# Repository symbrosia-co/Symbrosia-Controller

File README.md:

# The Symbrosia Controller
As originally designed, the Symbrosia Controller is a low cost, robust, controller designed for aquaculture.  Initially developed to support on-shore seaweed farming operations in Kailua Kona, Hawai'i, the Symbrosia Controller features a customized, low-cost sensor suite and integrated control functions tailored to meet the unique demands of these environments. 

In addition to commercial use, we envision the Symbrosia Controller as a powerful educational tool. By promoting literacy in electronics, programming, and agricultural management, we hope to empower individuals and communities to innovate and thrive in the agricultural sector. Our goal is to create a community where knowledge and technology are shared to drive sustainable agricultural practices and food security worldwide.

## Background
The Symbrosia controller was developed for in-house use as a lower-cost alternative to the PLC-based and commercial off-the-shelf systems we use for algae tank and bioreactor control.  In addition to controlling the tanks there were a few other needs, places where a little remote control and monitoring is invaluable.  With the availability of WiFi processors like the ESP32 automating these functions was a practical option.

Thus the Symbrosia Controller was born…  An ESP32 wedded to a circuit board that contains the most commonly needed interfaces. A water quality sensor amplifier, some temperature inputs, a couple analog inputs, along with some relays and transistor outputs for controlling external devices like valves and pumps. 

While there are commercial solutions available, we have had mixed experience with them... The available commercial controllers are expensive and tend to provide “closed garden” systems where it becomes difficult to retrieve data outside of dedicated application software.  There is also limited or no support for integrating this equipment into a wider system.  While a number of small-scale, open source solutions do exist, none of the devices we have reviewed are fully developed into robust, industrial solutions.  As a result of our experience the Symbrosia controller offers a number of key advantages…

+ Designed from the ground up as a network appliance with full WiFi access.
+ A standard industrial ModbusTCP interface, a well established interface supported by a vast array of software and solutions available in the market.
+ A simple and effective user interface allowing access to key settings.
+ A well thought out and flexible control arrangement allowing automated control of pH, temperature, or other parameters.
+ A range of inputs that address the usual aquaculture needs...
  + One fully isolated water quality amplifier (for pH, ORP, etc.)
  + Two Pt100 temperature inputs
  + Two general purpose analog inputs that can be used with 0-5V, 0-10V, or 4-20mA signals, these can also be used as simple digital inputs.
  + Two relay outputs
  + Two open collector digital outputs
+ Good calibration solutions in place for the analog inputs
+ Semi-automated pH calibration built into the software for use with 7ph, and 4pH or 10pH reference solutions.
+ A complete solution ready for deployment in real applications.  Use it as designed and published, or change the hardware or code to suit your own needs.

Communication is via 2.4GHz WiFi, thus no cabling beyond power, or perhaps your sensors is required, a very real concern when salt water is involved and locations are scattered across a large facility. 2.4GHz offers much increased range for applications that do not require the bandwidth of higher frequencies.

For remote monitoring a ModbusTCP interface is implemented.  This allows easy integration with custom software or standard industrial SCADA systems.  While most programming languages like Python have ModbusTCP libraries available to allow connections with a few lines of code.

There are many options for designing and building a device like this.  The philosophy used in the design was carefully considered...

+ The controller is designed to be constructed and maintained by anyone with modest electronics knowledge and skills. Unless changing features is desired, no programming is required to set up and use the controller.
+ Complex solutions or specialized parts were avoided.  Rather parts that are commonly available, inexpensive, and likely to remain available for some time to come were chosen for the design.
+ An open source programming platform is used so that development tools are available at no cost, specifically the Arduino platform.
+ An open source schematic capture PCB CAD package was used, specifically KiCad. The CAD files may be used or edited at no cost beyond learning to use the software.

An example of the commonly available part philosophy can be found in the display.  There was great temptation to use a newer OLED color graphical display that would be both fun and attractive.  Rather a mundane 16x2 LCD character display was chosen.  The LDC display is very standard, inexpensive, robust in outdoor settings, available from multiple vendors, and is likely to remain available for a decade or two.  Still, a version based on an OLED display may exist someday just for the fun of it.

Another good example of this is in using a development module for the ESP32 rather than laying out the ESP32 and support electronics directly onto the main PCB.  While much of the design is surface mount, larger packages were used, this allows the entire PCB to be assembled by hand with no more specialized equipment than a decent soldering iron.

Likewise using the Arduino programming platform provides an approachable simplicity that is easily learned.  A huge array of support exists on the web with a robust development community.  Libraries to support Arduino are available from many sources that allow the use of a wide array of sensors, chips, or ready to use modules.

With the controller proving its usefulness across our algae production facility a further decision was made…  To release the controller to the community as an open source device.  Symbrosia is publishing the complete plans…  Schematic, BOM, PCB, 3D models, code, and user manual.

There is nothing exotic or particularly special here.  The Symbrosia Controller is the result of taking a number of parts and solutions that are available in the community and weaving them into a well thought out and robust solution.  The controller has been a good solution for us, maybe you can use it as well.

The Symbrosia Team

## Hardware
The Symbrosia Controler is a single circuit board that measures 120 x 92mm (4.71" x 3.62").  The board mounts an LCD display, a rotaty encoder for user input, and a pair of 8 circuit headers that permit easy connection of power and field wiring.  

The PCB assembly is designed to be mounted in either a simple case for DIN rail mounting, or for direct mounting in a control panel where the display and control knob are easily accessible.  Examples of both of these mountings can be found in the documention here including 3D models for the case.

## Software
There are several software elements to the controller, all can be found in this repository.  While you may simply download everything here, an easier solution would be to install a copy of [GitHub desktop](https://desktop.github.com/download/).  Synchronizing with Github would allow you to keep an always up-to-date version available for use.

### Firmware
Firmware for the Symbrosia Controller was wriiten in the Arduino Framework for ESP-32.  The Arduino ecosystem is open source, free, and is amazing well supported by an enormous user community.  If you do not know how to use an Arduino device it is a good skill to learn, an incredibly useful tool to have in your skillset.

Compiling and downloading firmware to the controller is most easily accomplished by downloading the free [Arduino IDE](https://www.arduino.cc/en/software) and configuring it for use with the ESP32.  Additionally a few libraries will need to be loaded, this can be done with the library tool in the IDE.

### SyView
Setup and configuration is done through access to the Modbus regiaters.  Doing this by hand would be tedious.  To simplify this task SyView, a Python GUI is provided that gives easy access to all of the setup registers in an organized graphical app.  SyView also allows downloading complete configurations so they may be stored or loaded to multiple units with a single click. 

### MbMon
MbMon is a ModbusTCP data logger.  This script is often used to do simple datalogging for testing and short experiments.  An XML configuration file is used to designate a few Modbus devices on a local network.  The specified registers are monitored and if needed logged to a CSV file that can be used for data analysis.

MbMon will work with any ModbusTCP device including SymbCtrl, it can also serve as example code for writing your own logging application.

## Examples
Currently three sample systems are documented here, use these setups as is, or modify them to your own needs...

* [Tank or PBR controller](/samples/TankController/)
* [CO<sub>2</sub> Tapping Point Monitor](/samples/CO2Monitor/)
* [Weather Station](/samples/weather/)
  
Each of these designs are provided with schematics, 3D models, and setup files for the Symbrosia Controller.

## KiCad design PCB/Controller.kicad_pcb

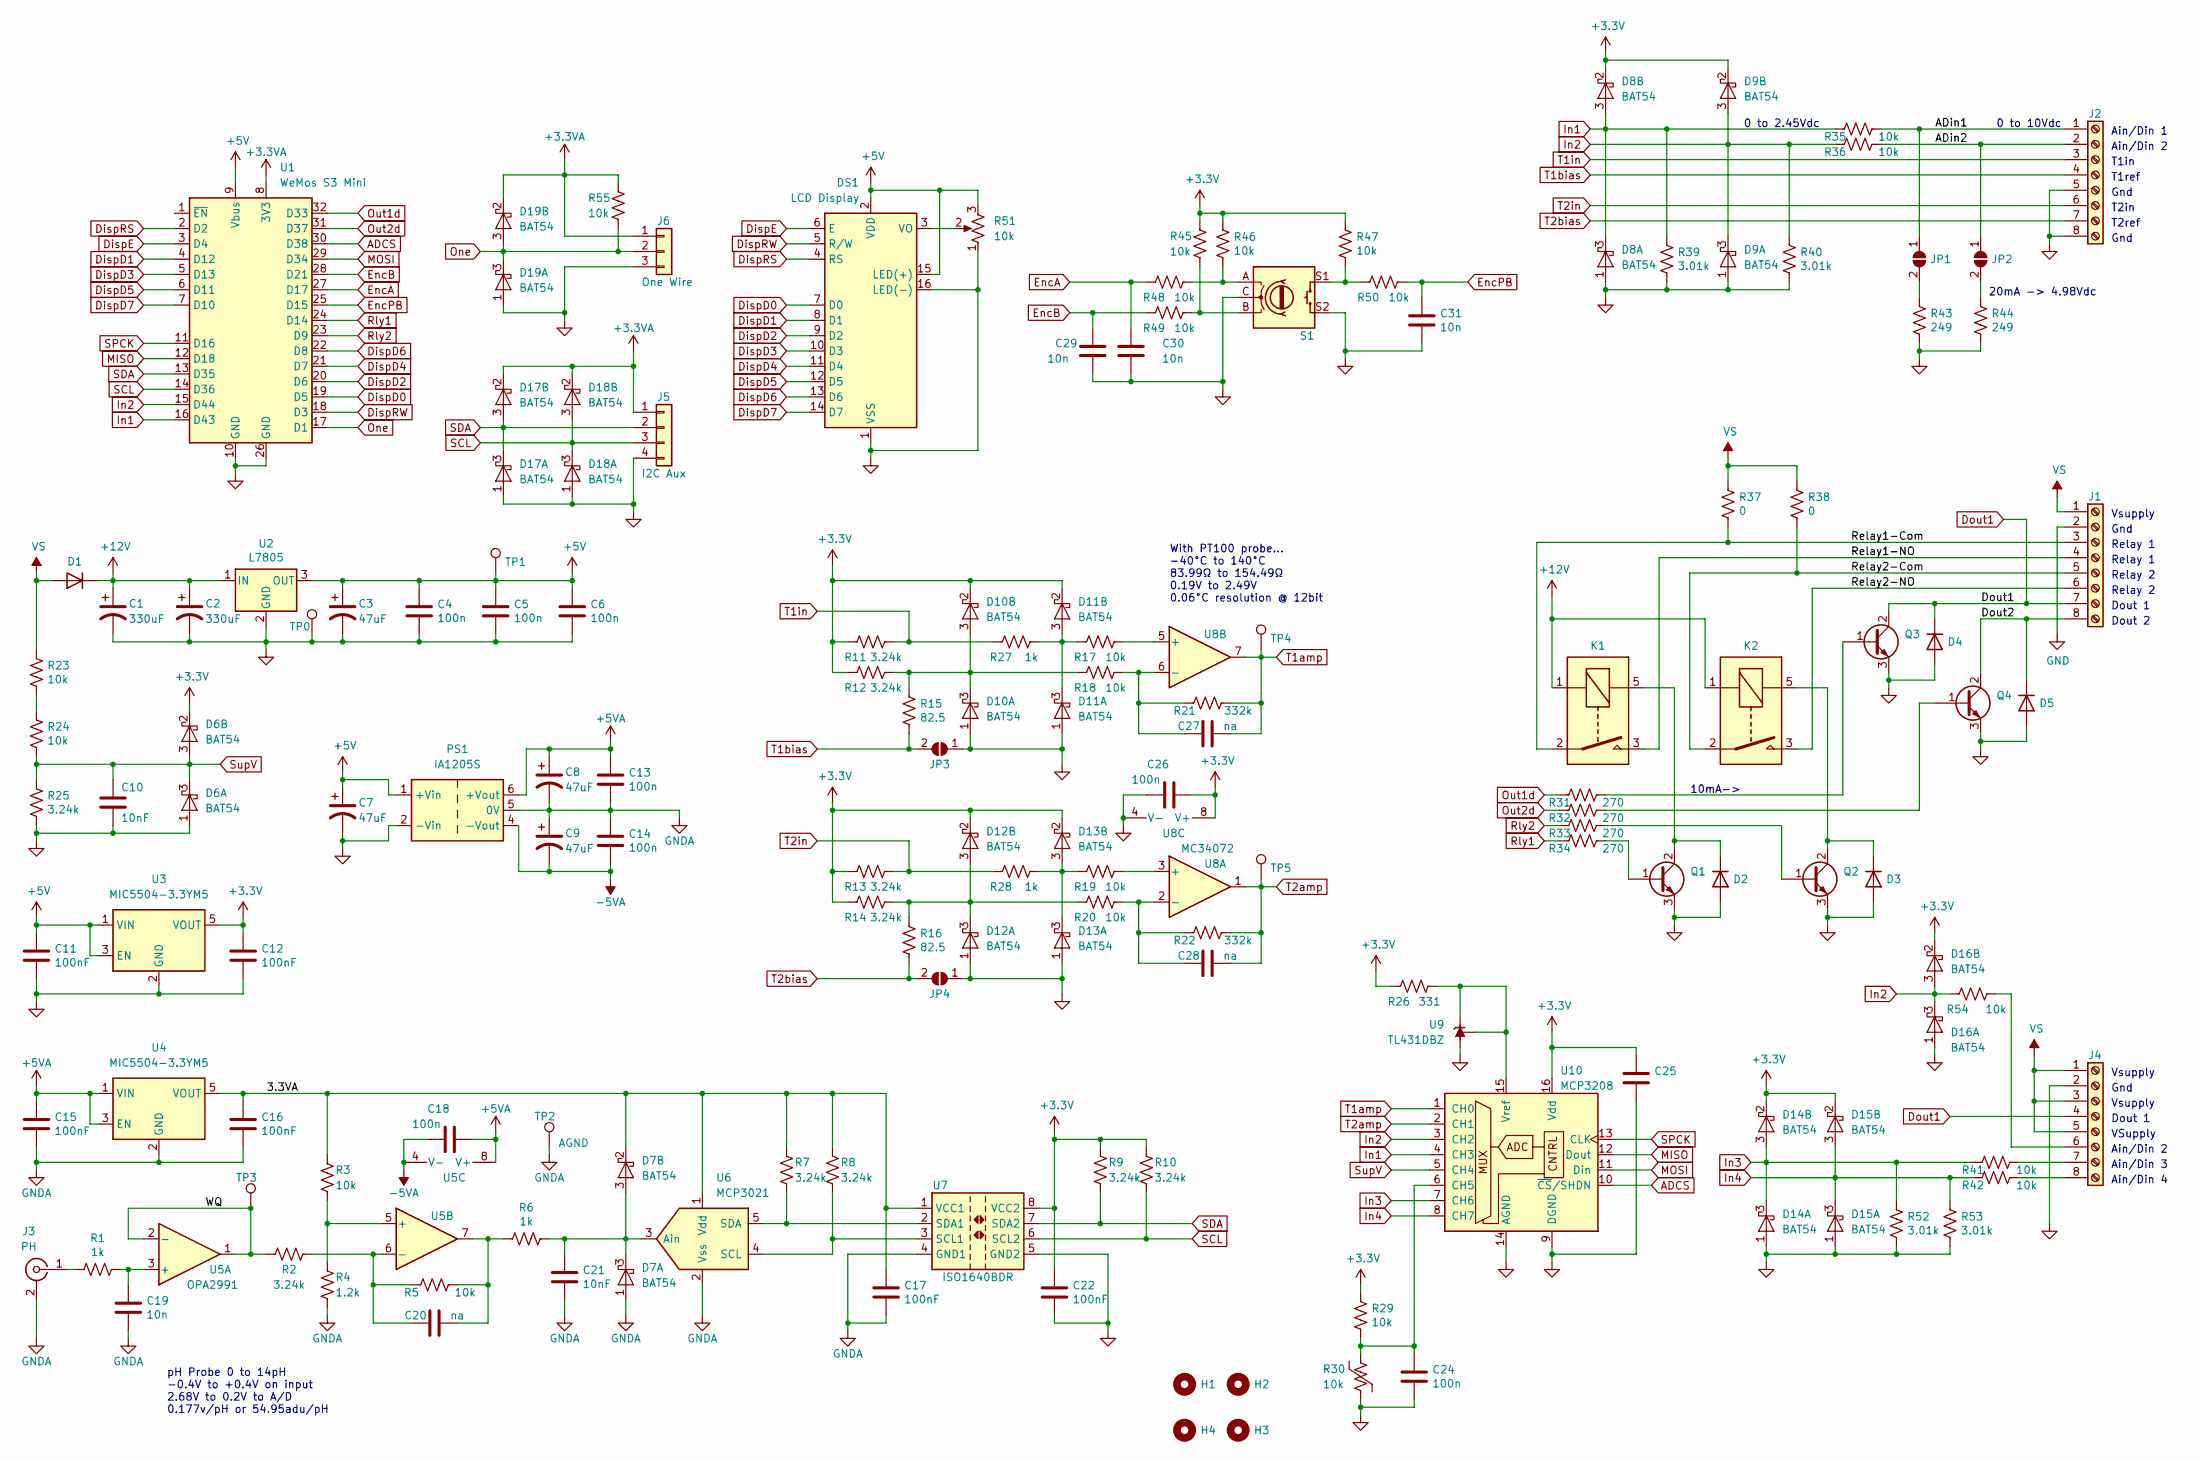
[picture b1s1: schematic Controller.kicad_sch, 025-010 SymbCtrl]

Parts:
C1, C2: 330uF; CP_Radial_D10.0mm_P5.00mm
C3, C7, C8, C9: 47uF; CP_Radial_D6.3mm_P2.50mm
C4, C5, C6, C13, C14, C18, C24, C25, C26: 100n; C_1206_3216Metric_Pad1.33x1.80mm_HandSolder
C10, C21: 10nF; C_1206_3216Metric_Pad1.33x1.80mm_HandSolder
C11, C12, C15, C16, C17, C22: 100nF; C_1206_3216Metric_Pad1.33x1.80mm_HandSolder
C19, C29, C30, C31: 10n; C_1206_3216Metric_Pad1.33x1.80mm_HandSolder
C20, C27, C28: na; C_1206_3216Metric_Pad1.33x1.80mm_HandSolder
D1, D2, D3, D4, D5: US1A; D_SMA
D6, D7, D8, D9, D10, D11, D12, D13, D14, D15, D16, D17, D18, D19: BAT54; SOT-23
DS1: LCD Display; WC1602A
H1, H2, H3, H4: MountingHole; MountingHole_3.5mm
J1, J2: Screw_Terminal_01x08; PhoenixContact_MSTBA_2,5_8-G-5,08_1x08_P5.08mm_Horizontal
J3: PH; BNC_Amphenol_B6252HB_Reversible
J4: Screw_Terminal_01x08; PhoenixContact_MSTBVA_2,5_8-G-5,08_1x08_P5.08mm_Vertical
J5: I2C Aux; Molex_KK-254_AE-6410-04A_1x04_P2.54mm_Vertical
J6: One Wire; Molex_KK-254_AE-6410-03A_1x03_P2.54mm_Vertical
JP1: In1 4-20; SolderJumper-2_P1.3mm_Open_RoundedPad1.0x1.5mm
JP2: In2 4-20; SolderJumper-2_P1.3mm_Open_RoundedPad1.0x1.5mm
JP3: T1 2/3Wire; SolderJumper-2_P1.3mm_Open_RoundedPad1.0x1.5mm
JP4: T2 2/3Wire; SolderJumper-2_P1.3mm_Open_RoundedPad1.0x1.5mm
K1, K2: TE_PCH-1xxx2M; Relay_SPST_TE_PCH-1xxx2M
PS1: IA1205S; Converter_DCDC_XP_POWER-IAxxxxS_THT
Q1, Q2, Q3, Q4: BCX56; SOT-89-3_Handsoldering
R1, R6, R27, R28: 1k; R_1206_3216Metric_Pad1.30x1.75mm_HandSolder
R2, R7, R8, R9, R10, R11, R12, R13, R14, R25: 3.24k; R_1206_3216Metric_Pad1.30x1.75mm_HandSolder
R3, R5, R17, R18, R19, R20, R23, R24, R29, R35, R36, R41, R42, R45, R46, R47, R48, R49, R50, R54, R55: 10k; R_1206_3216Metric_Pad1.30x1.75mm_HandSolder
R4: 1.2k; R_1206_3216Metric_Pad1.30x1.75mm_HandSolder
R15, R16: 82.5; R_1206_3216Metric_Pad1.30x1.75mm_HandSolder
R21, R22: 332k; R_1206_3216Metric_Pad1.30x1.75mm_HandSolder
R26: 331; R_1206_3216Metric_Pad1.30x1.75mm_HandSolder
R30: 10k; R_0805_2012Metric_Pad1.20x1.40mm_HandSolder
R31, R32, R33, R34: 270; R_1206_3216Metric_Pad1.30x1.75mm_HandSolder
R37, R38: 0; R_1206_3216Metric_Pad1.30x1.75mm_HandSolder
R39, R40, R52, R53: 3.01k; R_1206_3216Metric_Pad1.30x1.75mm_HandSolder
R43, R44: 249; R_1210_3225Metric_Pad1.30x2.65mm_HandSolder
R51: 10k; Potentiometer_Piher_PT-6-V_Vertical_Hole
S1: RotaryEncoder_Switch; RotaryEncoder_Alps_EC11E-Switch_Vertical_H20mm_CircularMoun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
TP0: Gnd; TestPoint_THTPad_D2.5mm_Drill1.2mm
TP1: +5V; TestPoint_THTPad_D2.5mm_Drill1.2mm
TP2: AGND; TestPoint_THTPad_D2.5mm_Drill1.2mm
TP3: WQ; TestPoint_THTPad_D2.5mm_Drill1.2mm
TP4: Temp2; TestPoint_THTPad_D2.5mm_Drill1.2mm
TP5: Temp1; TestPoint_THTPad_D2.5mm_Drill1.2mm
U1: WeMos S3 Mini; WEMOS S2 Mini
U2: L7805; TO-220-3_Horizontal_TabDown
U3, U4: MIC5504-3.3YM5; SOT-23-5_HandSoldering
U5: OPA2991; SOIC-8_3.9x4.9mm_P1.27mm
U6: MCP3021; SOT-23-5_HandSoldering
U7: ISO1640BDR; SO-8_3.9x4.9mm_P1.27mm
U8: MC34072; SOIC-8_3.9x4.9mm_P1.27mm
U9: TL431DBZ; SOT-23
U10: MCP3208; SOIC-16_3.9x9.9mm_P1.27mm

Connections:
+3.3V: C12.1, C22.1, C25.1, C26.1, D6.2 (K), D8.2 (K), D9.2 (K), D10.2 (K), D11.2 (K), D12.2 (K), D13.2 (K), D14.2 (K), D15.2 (K), D16.2 (K), R9.1, R10.1, R11.1, R12.1, R13.1, R14.1, R26.1, R29.2, R45.2, R46.2, R47.2, U3.5 (VOUT), U7.8 (VCC2), U8.8 (V+), U10.16 (Vdd)
+3.3VA: D17.2 (K), D18.2 (K), D19.2 (K), J5.1, J6.1, R55.2, U1.8 (3V3)
+5V: C3.1, C4.1, C5.1, C6.1, C7.1, C11.1, DS1.2 (VDD), DS1.15 (LED(+)), PS1.1 (+Vin), R51.3, TP1.1, U1.9 (Vbus), U2.3 (OUT), U3.1 (VIN), U3.3 (EN)
+5VA: C8.1, C13.1, C15.1, C18.1, PS1.6 (+Vout), U4.1 (VIN), U4.3 (EN), U5.8 (V+)
+12V: C1.1, C2.1, D1.1 (K), K1.1, K2.1, U2.1 (IN)
-5VA: C9.2, C14.2, C18.2, PS1.4 (-Vout), U5.4 (V-)
/3.3VA: C16.1, C17.1, D7.2 (K), R3.1, R7.1, R8.1, U4.5 (VOUT), U6.1 (Vdd), U7.1 (VCC1)
/ADin1: J2.1, JP1.1 (A), R35.2
/ADin2: J2.2, JP2.1 (A), R36.2
/Dout2: D5.1 (K), J1.8, Q4.2 (C)
/Relay1-Com: J1.3, K1.2, R37.1
/Relay1-NO: J1.4, K1.3
/Relay2-Com: J1.5, K2.2, R38.1
/Relay2-NO: J1.6, K2.3
/WQ: R2.2, TP3.1, U5.1, U5.2 (-)
ADCS: U1.30 (D38), U10.10 (~CS/SHDN)
DispD0: DS1.7 (D0), U1.19 (D5)
DispD1: DS1.8 (D1), U1.4 (D12)
DispD2: DS1.9 (D2), U1.20 (D6)
DispD3: DS1.10 (D3), U1.5 (D13)
DispD4: DS1.11 (D4), U1.21 (D7)
DispD5: DS1.12 (D5), U1.6 (D11)
DispD6: DS1.13 (D6), U1.22 (D8)
DispD7: DS1.14 (D7), U1.7 (D10)
DispE: DS1.6 (E), U1.3 (D4)
DispRS: DS1.4 (RS), U1.2 (D2)
DispRW: DS1.5 (R/W), U1.18 (D3)
Dout1: D4.1 (K), J1.7, J4.4, Q3.2 (C)
EncA: C30.1, R48.1, U1.27 (D17)
EncB: C29.1, R49.1, U1.28 (D21)
EncPB: C31.1, R50.2, U1.25 (D15)
GND: C1.2, C2.2, C3.2, C4.2, C5.2, C6.2, C7.2, C10.2, C11.2, C12.2, C22.2, C24.2, C25.2, C26.2, C29.2, C30.2, C31.2, D2.2 (A), D3.2 (A), D4.2 (A), D5.2 (A), D6.1 (A), D8.1 (A), D9.1 (A), D10.1 (A), D11.1 (A), D12.1 (A), D13.1 (A), D14.1 (A), D15.1 (A), D16.1 (A), D17.1 (A), D18.1 (A), D19.1 (A), DS1.1 (VSS), DS1.16 (LED(-)), J1.2, J2.5, J2.8, J4.2, J5.4, J6.3, JP3.1 (A), JP4.1 (A), PS1.2 (-Vin), Q1.3 (E), Q2.3 (E), Q3.3 (E), Q4.3 (E), R25.1, R30.2, R39.1, R40.1, R43.1, R44.1, R51.1, R52.1, R53.1, S1.C, S1.S2, TP0.1, U1.10 (GND), U1.26 (GND), U2.2 (GND), U3.2 (GND), U7.5 (GND2), U8.4 (V-), U9.3 (A), U10.9 (DGND), U10.14 (AGND)
GNDA: C8.2, C9.1, C13.2, C14.1, C15.2, C16.2, C17.2, C19.2, C21.2, D7.1 (A), J3.2 (Ext), PS1.5 (0V), R4.2, TP2.1, U4.2 (GND), U6.2 (Vss), U7.4 (GND1)
In1: D8.3 (COM), R35.1, R39.2, U1.16 (D43), U10.4 (CH3)
In2: D9.3 (COM), D16.3 (COM), R36.1, R40.2, R54.1, U1.15 (D44), U10.3 (CH2)
In3: D14.3 (COM), R41.1, R52.2, U10.7 (CH6)
In4: D15.3 (COM), R42.1, R53.2, U10.8 (CH7)
MISO: U1.12 (D18), U10.12 (Dout)
MOSI: U1.29 (D34), U10.11 (Din)
unnamed: C20.1, R5.2, R6.2, U5.7
unnamed: D2.1 (K), K1.5, Q1.2 (C)
unnamed: D3.1 (K), K2.5, Q2.2 (C)
unnamed: C21.1, D7.3 (COM), R6.1, U6.3 (Ain)
unnamed: D10.3 (COM), R12.2, R15.2, R18.1
unnamed: D11.3 (COM), R17.1, R27.2
unnamed: D12.3 (COM), R14.2, R16.2, R20.1
unnamed: D13.3 (COM), R19.1, R28.2
unnamed: DS1.3 (VO), R51.2
unnamed: J3.1 (In), R1.2
unnamed: J4.6, R54.2
unnamed: J4.7, R41.2
unnamed: J4.8, R42.2
unnamed: JP1.2 (B), R43.2
unnamed: JP2.2 (B), R44.2
unnamed: Q1.1 (B), R34.2
unnamed: Q2.1 (B), R33.2
unnamed: Q3.1 (B), R31.2
unnamed: Q4.1 (B), R32.2
unnamed: R23.1, R24.2
unnamed: R45.1, R49.2, S1.B
unnamed: R46.1, R48.2, S1.A
unnamed: R47.1, R50.1, S1.S1
unnamed: C19.1, R1.1, U5.3 (+)
unnamed: R3.2, R4.1, U5.5 (+)
unnamed: C20.2, R2.1, R5.1, U5.6 (-)
unnamed: R8.2, U6.4 (SCL), U7.3 (SCL1)
unnamed: R7.2, U6.5 (SDA), U7.2 (SDA1)
unnamed: R19.2, U8.3 (+)
unnamed: C28.2, R20.2, R22.1, U8.2 (-)
unnamed: R17.2, U8.5 (+)
unnamed: C27.2, R18.2, R21.1, U8.6 (-)
unnamed: C24.1, R29.1, R30.1, U10.6 (CH5)
unnamed: R26.2, U9.1 (K), U9.2 (REF), U10.15 (Vref)
One: D19.3 (COM), J6.2, R55.1, U1.17 (D1)
Out1d: R31.1, U1.32 (D33)
Out2d: R32.1, U1.31 (D37)
Rly1: R34.1, U1.24 (D14)
Rly2: R33.1, U1.23 (D9)
SCL: D18.3 (COM), J5.3, R10.2, U1.14 (D36), U7.6 (SCL2)
SDA: D17.3 (COM), J5.2, R9.2, U1.13 (D35), U7.7 (SDA2)
SPCK: U1.11 (D16), U10.13 (CLK)
SupV: C10.1, D6.3 (COM), R24.1, R25.2, U10.5 (CH4)
T1amp: C27.1, R21.2, TP4.1, U8.7, U10.1 (CH0)
T1bias: J2.4, JP3.2 (B), R15.1
T1in: J2.3, R11.2, R27.1
T2amp: C28.1, R22.2, TP5.1, U8.1, U10.2 (CH1)
T2bias: J2.7, JP4.2 (B), R16.1
T2in: J2.6, R13.2, R28.1
VS: D1.2 (A), J1.1, J4.1, J4.3, J4.5, R23.2, R37.2, R38.2

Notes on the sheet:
Gnd
Ain/Din 4
Dout 1
0 to 2.45Vdc
Relay 2
T2in
Vsupply
T2ref
20mA -> 4.98Vdc
Ain/Din 1
T1in
Relay 1
Ain/Din 2
pH Probe 0 to 14pH -0.4V to +0.4V on input 2.68V to 0.2V to A/D 0.177v/pH or 54.95adu/pH
VSupply
Ain/Din 3
10mA->
0 to 10Vdc
Dout 2
With PT100 probe... -40°C to 140°C 83.99Ω to 154.49Ω 0.19V to 2.49V 0.06°C resolution @ 12bit
T1ref

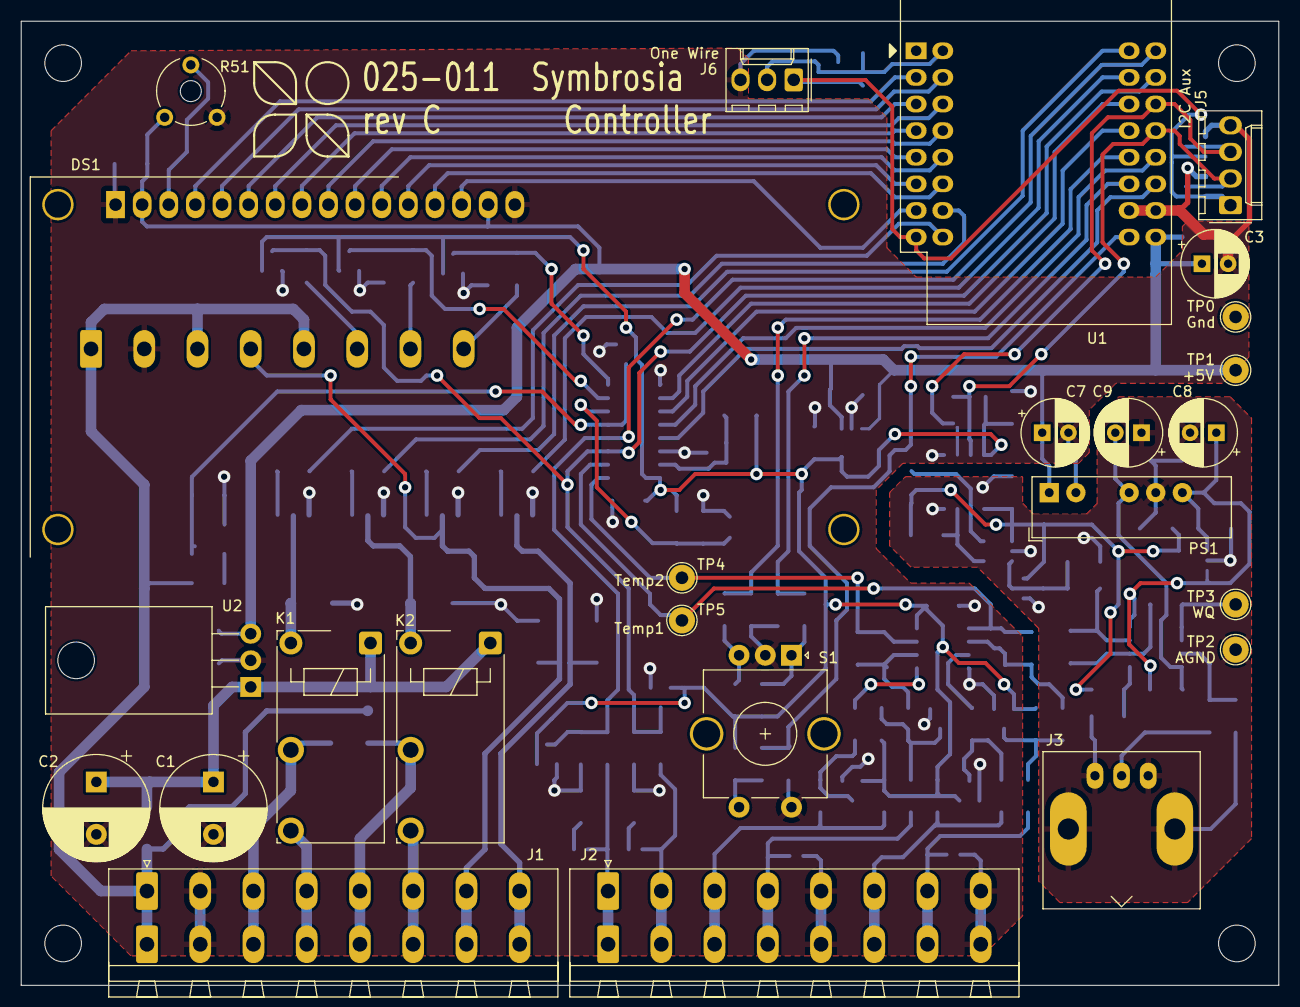
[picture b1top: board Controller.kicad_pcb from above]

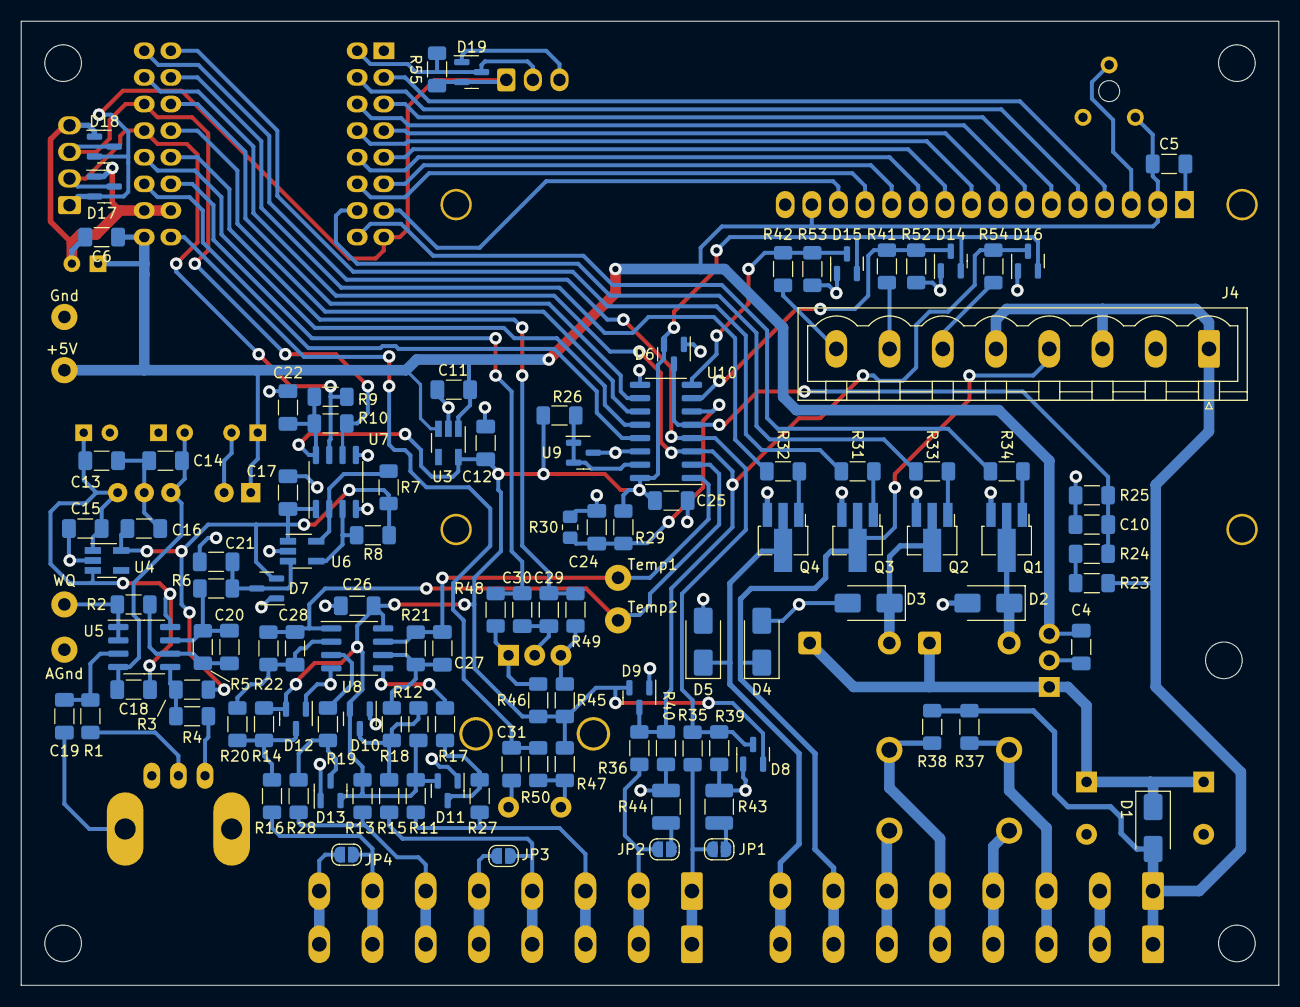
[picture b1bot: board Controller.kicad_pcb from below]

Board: 2 copper layers, 120.0 x 92.0 mm, 143 parts (114 on the bottom side), 89 nets.

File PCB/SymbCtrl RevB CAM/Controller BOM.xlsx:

Comment | Designator | Footprint | JLCPCB
Ceramic capacitor, 100nF 50V 1206 | C4, C5, C6, C10, C11, C12, C13, C14, C15, C16, C17, C18, C22, C24, C25, C26 | 1206 | C24497
Ceramic capacitor, 10nF 50V 1206 | C21, C29, C30, C31 | 1206 | C521245
Ceramic capacitor, 1nF 50V 1206 | C20, C27, C28 | 1206 | C107207
Rectifier diode, 100V 1A SMA | D1, D2, D3, D4, D5 | SMA | C156295
Schottky diode 30V 100mA dual series SOT23 | D6, D7, D8, D9, D10, D11, D12, D13 | SOT-23 | C47546
NPN Transistor 40V 1A SOT89 | Q1, Q2, Q3, Q4 | SOT-89-3 | C460011
1.00kΩ 1% resistor, 1/4W 1206 | R1, R6, R27, R28, R31, R32, R33, R34 | 1206 | C131398
3.24kΩ 1% resistor, 1/4W 1206 | R2, R7, R8, R9, R10, R11, R12, R13, R14, R25 | 1206 | C488775
10.0kΩ 1% resistor, 1/4W 1206 | R3, R5, R17, R18, R19, R20, R23, R24, R29, R35, R36, R45, R46, R47, R48, R49, R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 | 1206 | C132649
1.20kΩ 1% resistor, 1/4W 1206 | R4 | 1206 | C185265
82.5Ω 1% resistor, 1/4W 1206 | R15, R16 | 1206 | C229817
332kΩ 1% resistor, 1/4W 1206 | R21, R22 | 1206 | C137311
331Ω 1% resistor, 1/4W 1206 | R26 | 1206 | C114944
10kΩ thermistor 1206 B25/85 3630K | R30 | 1208 | C525390
3.01kΩ 1% resistor, 1/4W 1206 | R39, R40 | 1206 | C229594
249Ω 1% resistor, 1/2W 1210 | R43, R44 | 1210 | C723700
MIC5504 3.3V regulator, SOT23 | U3, U4 | SOT-23-5 | C88419
Dual op-amp, low Ib, SOIC-8 | U5, U8 | SOIC-8 | C2878324
MCP3021 10bit AtoD, SOT23-5 | U6 | SOT-23-5 | C128576
ISO1640BDR isolated I2C | U7 | SOIC-8 | C5122339
TL431 programmable voltage reference, SOIC-8 | U9 | SOIC-8 | C6970
MCP3208 12 bit 8 channel AtoD | U10 | SOIC-16 | C16939

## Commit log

2024-08-03 Update LICENSE.md
    Use GPLv3
2024-08-03 Create SymbCtrl.ino
    Added to GitHub
2024-08-03 Add files via upload
    Add source files to GitHub
2024-08-03 Add files via upload
    Add user manual to repository
2024-08-03 Update LICENSE.md
    Add full text for GPLv3
2024-08-03 Create resources
2024-08-03 Add files via upload
    Add a couple photos of the controller
2024-08-03 Add files via upload
    Smaller version of the photos
2024-08-03 Update README.md
    Further work on the readme
2024-08-03 Create README.md
    Initial outline written
2024-08-03 Update README.md
    Add more material
2024-08-04 Delete src directory
    Rearrange to make downloading to the Arduino IDE possible
2024-08-04 Create README.md
    Rearrange to make integration with Arduino IDE possible
2024-08-04 Create README.md
    New content
2024-08-04 Add files via upload
    Initial commit
2024-08-04 Delete SyView/lib/symbCtrlModbus.py.bak
    Not needed
2024-08-04 Delete SyView/lib/__pycache__ directory
    Not needed
2024-08-04 Update README.md
    Inital version
2024-08-04 Create README.md
    Initial version
2024-08-04 Update README.md
    Initial version
2024-08-04 Initial upload
2024-08-05 Add units
2024-08-05 Link latest from development PC
2024-08-05 Mods ro analogCtrl
    Added auto I2C address search to analogCtrl for MCP3021
2024-08-06 Add MBMon to repository
2024-08-08 Add some comments
2024-08-25 Add Weather
2024-08-25 Ignore configuration files
2024-09-01 Weather development
2024-09-04 Update ignore
2024-09-26 Config file update
2024-09-27 PBR Example
2024-09-27 Add STL files for PBR Controller
2024-09-27 Remove spaces from filenames
2024-09-27 Add PBR documentation
2024-10-09 Working on v2.7
2024-10-24 Create SyCheck
2024-10-24 Work on SyCheck
2024-10-24 Working on 2.7
2024-10-26 SyCheck Work
2024-10-26 Weather data
2024-10-28 v2.7 work
2024-10-28 Edit revision record
2024-10-29 Finalizing v2.7
2024-10-31 SyCheck v0.2
2024-10-31 SyView fixes
2024-11-01 Remove logfiles
2024-11-01 Version 2.7 work
2024-11-02 Regression test v2.7
2024-11-02 Edit rev record
2024-11-02 Set up FOTA
2024-11-02 Sync main
2024-11-02 Remove crud
2024-11-02 Revert "Edit rev record"
    This reverts commit 24d97c7264457223542c1ffbeaa103c3e2f5fb02.
2024-11-02 Rev check on v2.7
2024-11-02 QA on main after v2.7 merge
2024-11-05 v2.8 work
2024-11-07 Add Echo logic to memory.h limits
2024-11-14 SyView 1.3
    Add manual IP address selection
2024-11-15 Final v2.8!!
    FOTA is now operational, version needs a final regression test
2024-11-16 Fixes to v2.8 prerelease
2024-11-16 Prerelease v2.8 fixes
2024-11-18 Bug hunt in v2.8
2024-11-18 Work on v2.8
2024-11-18 Testing v2.8
2024-11-18 JSON Update
2024-11-19 v2.8 Final
2024-11-19 Update Binaries
2024-11-19 Add PCB image
2024-11-19 Cleanup uneeded filed
2024-11-21 Update comments
2025-04-15 Scrollable data frame
2025-04-16 Bind mouse wheel to scrolling
2025-04-18 Sync it
2025-04-25 Tweaks to MBMon
2025-04-30 MBMon Work v1.3
2025-05-03 MBMon work
2025-05-09 MBMon2 Work
2025-05-10 MBMon2 Work
    Nearing release of MBMon2
2025-05-11 MBMon Fix Scrolling
2025-05-11 MBMon bughunting
2025-05-15 SymbCtrl v2.9 work
2025-05-16 Update LinkedCtrl
2025-05-29 SyScan library module work
2025-05-30 SyView 2.0 work
2025-05-30 Release SyView 2.0 and Cleanup
2025-05-30 SyView 2.0 Release
2025-05-30 Backup Old MBMon
2025-06-03 Add PCB to repository
2025-06-04 PCB Rev C in work
2025-06-05 SymbCtrl 2.9 work
2025-06-16 Final SymbCtrl v2.9
2025-06-16 SymbCtrl 2.9 binaries for OTA update
2025-06-16 SymbCtrl 2.9 binaries for update
2025-06-19 SymbCtrlScan bugfix
2025-07-10 Update to MBMon
2025-07-15 Repository Cleanup
2025-07-15 Load images for docs
2025-07-15 MBMon Documentation
2025-07-15 Documentation work
2025-07-16 Documantation
2025-07-16 Documentation
2025-10-17 Minor
2026-03-02 Commenting updates
